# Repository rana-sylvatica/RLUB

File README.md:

# RLUB

The RLUB is a USBC breakout board designed for DIY rectangle controllers to facilitate the use of both USBC to GC and USBC to USBA cables using a single port.    

It is a derivation of the [HTUB](https://github.com/HTangl/HTUB) design made by [Hadoe](https://github.com/HTangl/) which in turn is based on the design of the [Model U](https://github.com/Crane1195/Model-U/tree/main) made by [Crane](https://github.com/Crane1195). 

Compared to the original Model U, an MBR120 diode has been added to this board along with a dedicated VSYS pin so you do not need to wire in a diode if you are using a Raspberry Pi Pico as your microcontroller. Simply wire the VSYS pin on the RLUB directly to the VSYS pin on the Pico.  

The TX- and RX- pins have also been removed as they are generally not used for most DIY rectangles.  

The mounting holes are for M3 screws and are 3.2mm in diameter.  

The RLUB modifies the HTUB design by putting all the pins in a single row which enables a low-profile connection to a mainboard with right-angle dupont connectors.

If you're not sure how to order these, Hadoe wrote a [guide](https://github.com/HTangl/Model-U) that explains how to get these fabricated by JLCPCB. The proccess is essentially the same for both the Model U and the RLUB with the one exception being you **MUST USE 0.8mm BOARD THICKNESS**. If you order these with the standard 1.6 board thickness JLC will not be able to manufacture them.  

This repo contains Gerber, BOM, and CPL files as well as the KiCad project files for a panel of 12 RLUB boards.

Other notes:

- These files were panelized with [KiKit](https://github.com/yaqwsx/KiKit)

- The USB port component is often out of stock on JLC.  However, it can be pre-ordered for a relatively low price, with a few weeks of lead time.

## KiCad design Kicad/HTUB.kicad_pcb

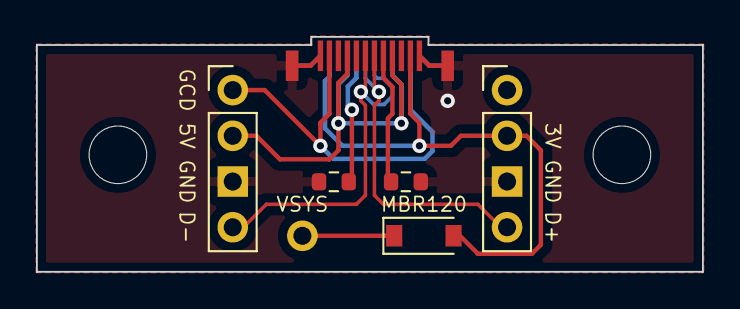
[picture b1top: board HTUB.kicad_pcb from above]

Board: 2 copper layers, 37.0 x 13.0 mm, 5 parts (0 on the bottom side), 9 nets.

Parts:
D1: MBR120; D_SOD-123
R1, R2: 5.1k; R_0603_1608Metric
U1: USB_C_Receptacle; Xunpu C2856665 USBC Straddle Mount
VSYS: PinHeader_1x01_P2.54mm_Vertical

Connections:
+3V3: D1.2 (A), U1.A2 (TX1+), U1.B2 (TX2+)
+5V: U1.A4 (VBUS), U1.A9 (VBUS), U1.B4 (VBUS), U1.B9 (VBUS)
D+: U1.A6 (D+), U1.B6 (D+)
D-: U1.A7 (D-), U1.B7 (D-)
GCD: U1.A11 (RX2+), U1.B11 (RX1+)
GND: R1.2, R2.2, U1.A1 (GND), U1.A12 (GND), U1.B1 (GND), U1.B12 (GND), U1.S1 (SHIELD)
unnamed: R1.1, U1.B5 (CC2)
unnamed: R2.1, U1.A5 (CC1)
VSYS: D1.1 (K), VSYS.1

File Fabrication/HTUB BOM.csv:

Comment,Designator,Footprint,LCSC
"MBR120","D1","Diode_SMD:D_SOD-123","C130880"
"5.1k","R1,R2","Resistor_SMD:R_0603_1608Metric","C23186"
"USB_C_Receptacle","U1","HTangl:Xunpu C2856665 USBC Straddle Mount","C2856665"

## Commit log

2022-04-23 Create LICENSE
2022-06-02 Change License to CERN
2023-01-27 Add 3x panel, change diode to in-stock part
